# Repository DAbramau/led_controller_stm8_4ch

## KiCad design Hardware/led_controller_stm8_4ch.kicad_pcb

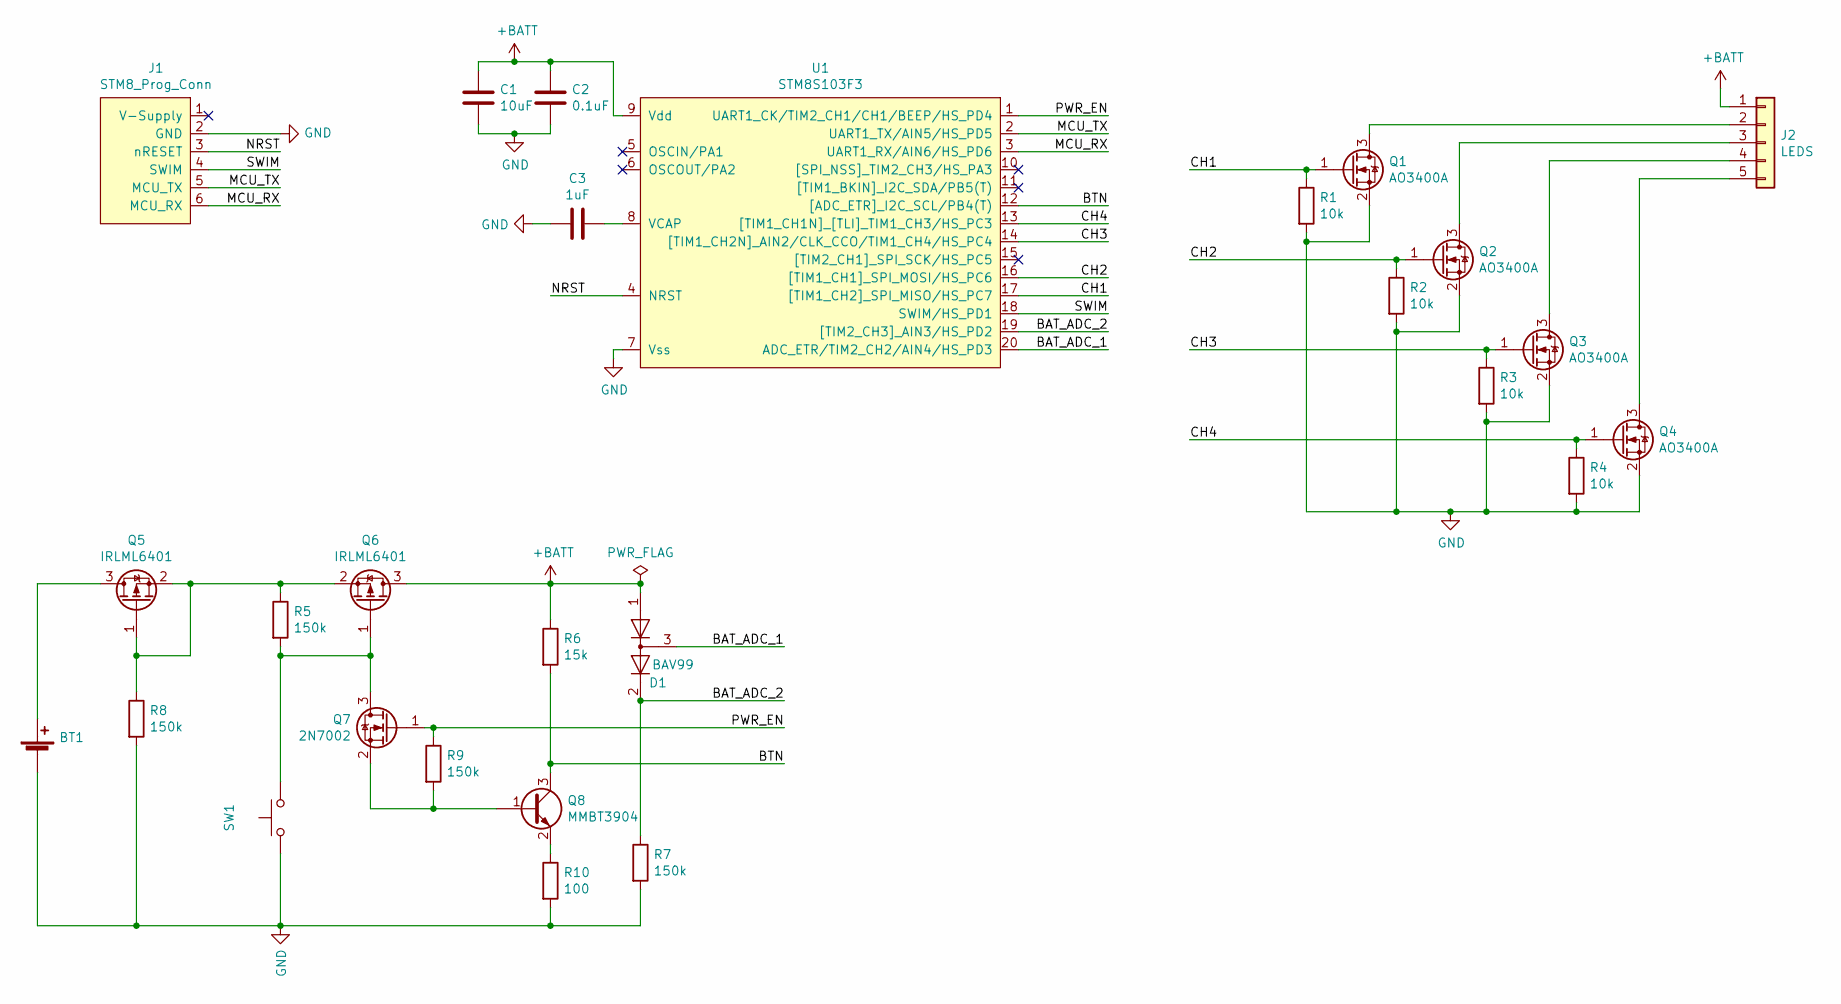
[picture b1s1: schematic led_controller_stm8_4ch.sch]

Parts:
BT1: Battery_Cell; CB_18650_PC2
C1: 10uF; C_0805_2012Metric_Pad1.15x1.40mm_HandSolder
C2: 0.1uF; C_0805_2012Metric_Pad1.15x1.40mm_HandSolder
C3: 1uF; C_0805_2012Metric_Pad1.15x1.40mm_HandSolder
D1: BAV99; SOT-23
J1: STM8_Prog_Conn; IDC-1.27-6P
J2: LEDS; JST_XH_B5B-XH-A_1x05_P2.50mm_Vertical
Q1, Q2, Q3, Q4: AO3400A; SOT-23
Q5, Q6: IRLML6401; SOT-23
Q7: 2N7002; SOT-23
Q8: MMBT3904; SOT-23
R1, R2, R3, R4: 10k; R_0805_2012Metric_Pad1.15x1.40mm_HandSolder
R5, R7, R8, R9: 150k; R_0805_2012Metric_Pad1.15x1.40mm_HandSolder
R6: 15k; R_0805_2012Metric_Pad1.15x1.40mm_HandSolder
R10: 100; R_0805_2012Metric_Pad1.15x1.40mm_HandSolder
SW1: SW_Push; SW_PUSH_6mm_H13mm
U1: STM8S103F3; TSSOP-20_4.4x6.5mm_P0.65mm

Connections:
+BATT: C1.1, C2.1, D1.1 (K), J2.1, Q6.3 (D), R6.1, U1.9 (Vdd)
/BAT_ADC_1: D1.3 (K), U1.20 (ADC_ETR/TIM2_CH2/AIN4/HS_PD3)
/BAT_ADC_2: D1.2 (A), R7.1, U1.19 ([TIM2_CH3]_AIN3/HS_PD2)
/BTN: Q8.3 (C), R6.2, U1.12 ([ADC_ETR]_I2C_SCL/PB4(T))
/CH1: Q1.1 (G), R1.1, U1.17 ([TIM1_CH2]_SPI_MISO/HS_PC7)
/CH2: Q2.1 (G), R2.1, U1.16 ([TIM1_CH1]_SPI_MOSI/HS_PC6)
/CH3: Q3.1 (G), R3.1, U1.14 ([TIM1_CH2N]_AIN2/CLK_CCO/TIM1_CH4/HS_PC4)
/CH4: Q4.1 (G), R4.1, U1.13 ([TIM1_CH1N]_[TLI]_TIM1_CH3/HS_PC3)
/MCU_RX: J1.6 (MCU_RX), U1.3 (UART1_RX/AIN6/HS_PD6)
/MCU_TX: J1.5 (MCU_TX), U1.2 (UART1_TX/AIN5/HS_PD5)
/NRST: J1.3 (nRESET), U1.4 (NRST)
/PWR_EN: Q7.1 (G), R9.1, U1.1 (UART1_CK/TIM2_CH1/CH1/BEEP/HS_PD4)
/SWIM: J1.4 (SWIM), U1.18 (SWIM/HS_PD1)
GND: BT1.2 (-), C1.2, C2.2, C3.2, J1.2 (GND), Q1.2 (S), Q2.2 (S), Q3.2 (S), Q4.2 (S), R1.2, R2.2, R3.2, R4.2, R7.2, R8.2, R10.2, SW1.1, U1.7 (Vss)
unnamed: BT1.1 (+), Q5.3 (D)
unnamed: C3.1, U1.8 (VCAP)
unnamed: J2.2, Q1.3 (D)
unnamed: J2.3, Q2.3 (D)
unnamed: J2.4, Q3.3 (D)
unnamed: J2.5, Q4.3 (D)
unnamed: Q5.1 (G), Q5.2 (S), Q6.2 (S), R5.1, R8.1
unnamed: Q6.1 (G), Q7.3 (D), R5.2, SW1.2
unnamed: Q7.2 (S), Q8.1 (B), R9.2
unnamed: Q8.2 (E), R10.1

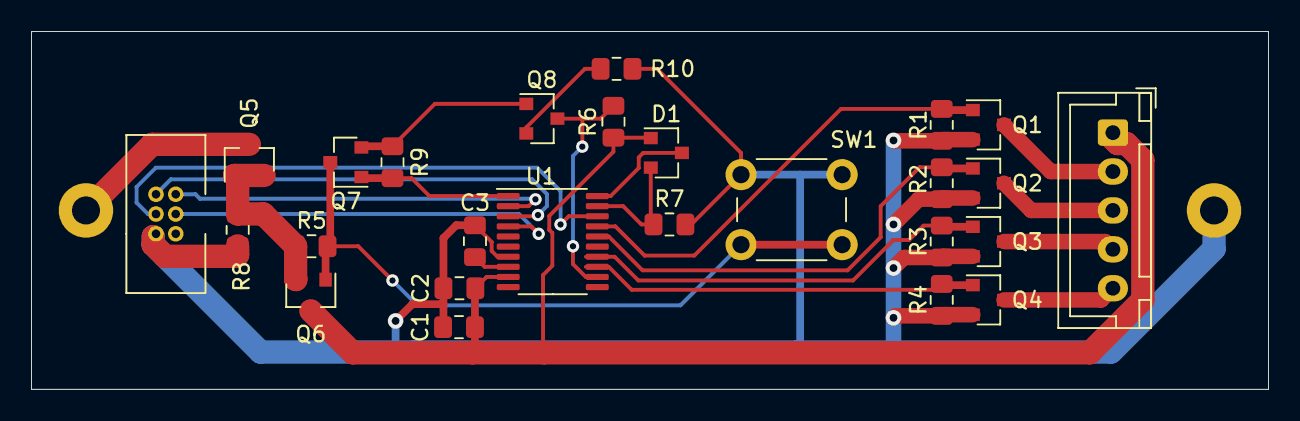
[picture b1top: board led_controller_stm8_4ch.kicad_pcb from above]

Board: 2 copper layers, 79.5 x 23.0 mm, 27 parts (1 on the bottom side), 24 nets.

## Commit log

2021-09-26 add pcb
2021-09-28 add battery protection
2021-09-28 fix PWR_EN pin
